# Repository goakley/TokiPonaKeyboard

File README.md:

# Toki Pona Keyboard

A 4-joystick input device, inspired by the sounds of [the Toki Pona language](https://tokipona.org/).

See [the website](https://goakley.github.io/TokiPonaKeyboard/) for more details on the keyboard, or the documentation in any of the subdirectories.

This project contains the following directories:

* `code` - The Arduino code that turns the hardware into a USB keyboard, plus other helpful tools
* `case` - The OpenSCAD files for the 3D model meant to house the electrical components of the keyboard
* `pcb`  - The KiCad project that defines the circuit board used in the keyboard
* `docs` - The project website and related documentation

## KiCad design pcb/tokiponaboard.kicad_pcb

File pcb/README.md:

# Toki Pona Keyboard - PCB

This directory contains the entire KiCad project that describes the keyboard PCB.

The `gerbers` directory contains the exported gerber and drill files that can be sent directly to a PCB manufacturer.

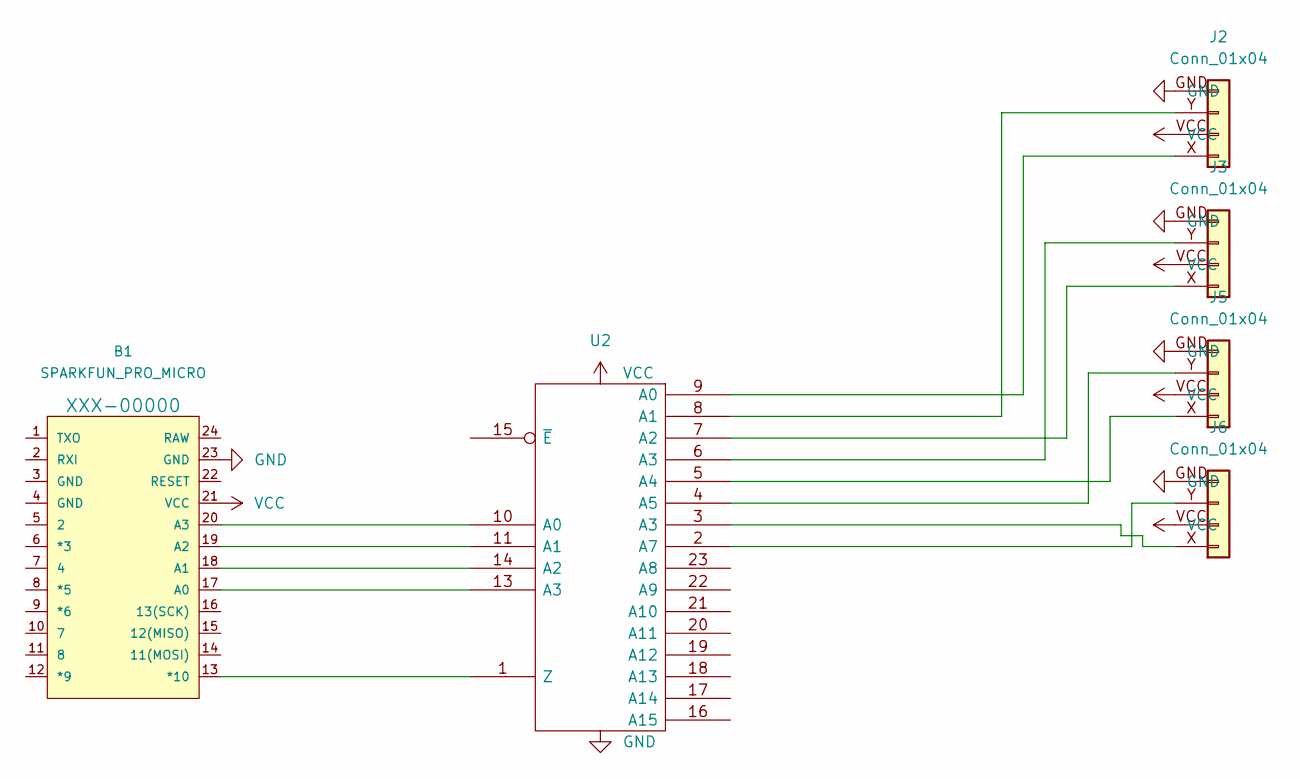
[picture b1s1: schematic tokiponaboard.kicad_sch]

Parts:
B1: SPARKFUN_PRO_MICRO
J2, J3, J5, J6: Conn_01x04; JOYSTICK-PSP1000
U2: (no value)

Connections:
GND: B1.23 (GND), J2.GND, J3.GND, J5.GND, J6.GND, U2.12 (Vss)
unnamed: B1.13 (*10), U2.1 (Z)
unnamed: B1.17 (A0), U2.13 (A3)
unnamed: B1.18 (A1), U2.14 (A2)
unnamed: B1.19 (A2), U2.11 (A1)
unnamed: B1.20 (A3), U2.10 (A0)
unnamed: J2.X, U2.9 (A0)
unnamed: J2.Y, U2.8 (A1)
unnamed: J3.X, U2.7 (A2)
unnamed: J3.Y, U2.6 (A3)
unnamed: J5.X, U2.5 (A4)
unnamed: J5.Y, U2.4 (A5)
unnamed: J6.X, U2.3 (A3)
unnamed: J6.Y, U2.2 (A7)
VCC: B1.21 (VCC), J2.VCC, J3.VCC, J5.VCC, J6.VCC, U2.24 (Vdd)

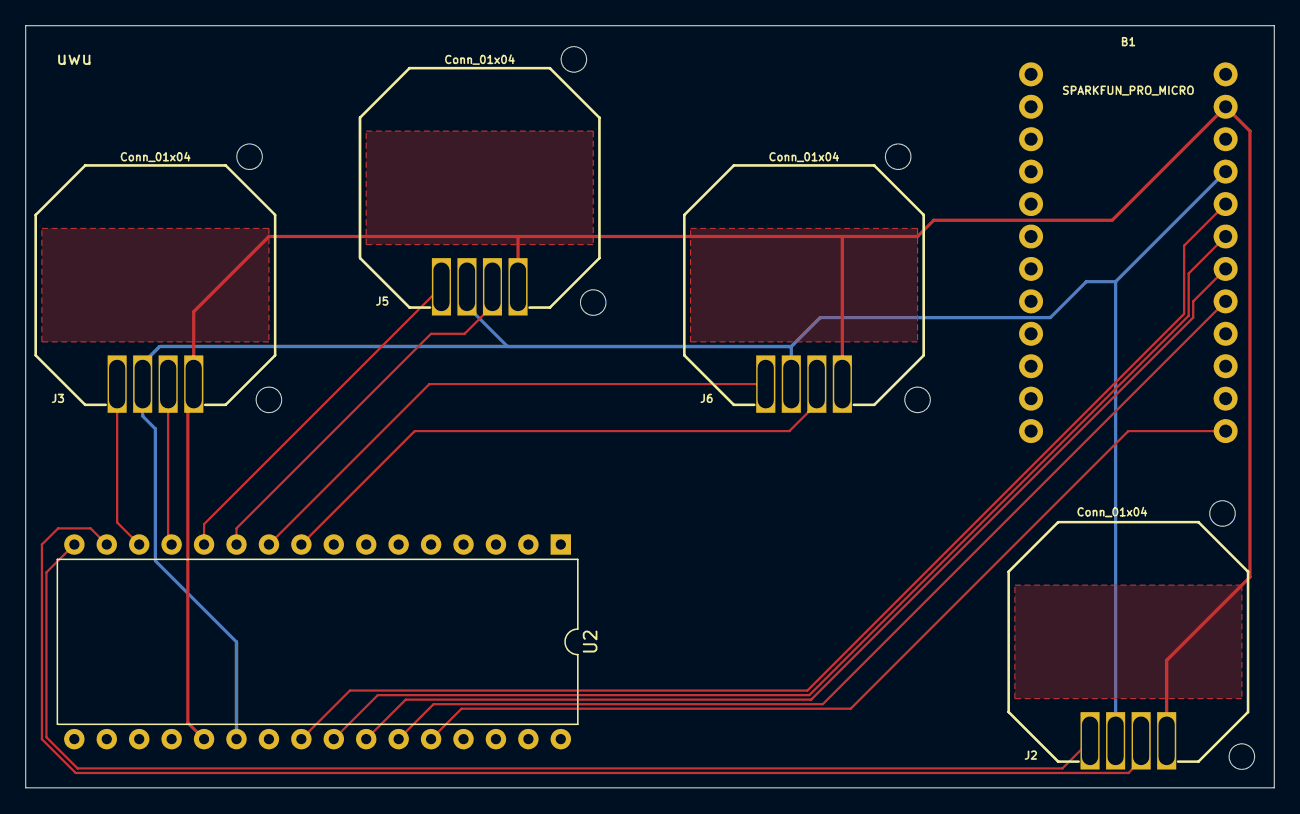
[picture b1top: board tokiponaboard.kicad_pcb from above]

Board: 2 copper layers, 97.8 x 59.7 mm, 6 parts (0 on the bottom side), 15 nets.

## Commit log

2022-04-20 Add case
2022-04-20 Clean up the openscad file
2022-04-20 add license
2022-04-20 Add code (arduino and keymap)
2022-05-02 Add website text
2022-05-02 Correct mapping software
2022-05-02 Run in keyboard mode by default
2022-05-02 Move "website" to "docs"
2022-05-02 Disable jekyll on github pages
2022-05-02 Add links to source code
2022-05-02 Add README with additional documentation
2022-05-02 Add missing control character from keymap
2022-05-02 Add demo video to the website
2022-05-02 Loop the website video
